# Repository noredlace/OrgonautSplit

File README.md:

# OrgonautSplit

A design by u/lizardsticks

A WIP split ergo board based off the orgonaut66. <br /> 

PCBs are mirrored to be utilized as a left and right.

KiCad Render

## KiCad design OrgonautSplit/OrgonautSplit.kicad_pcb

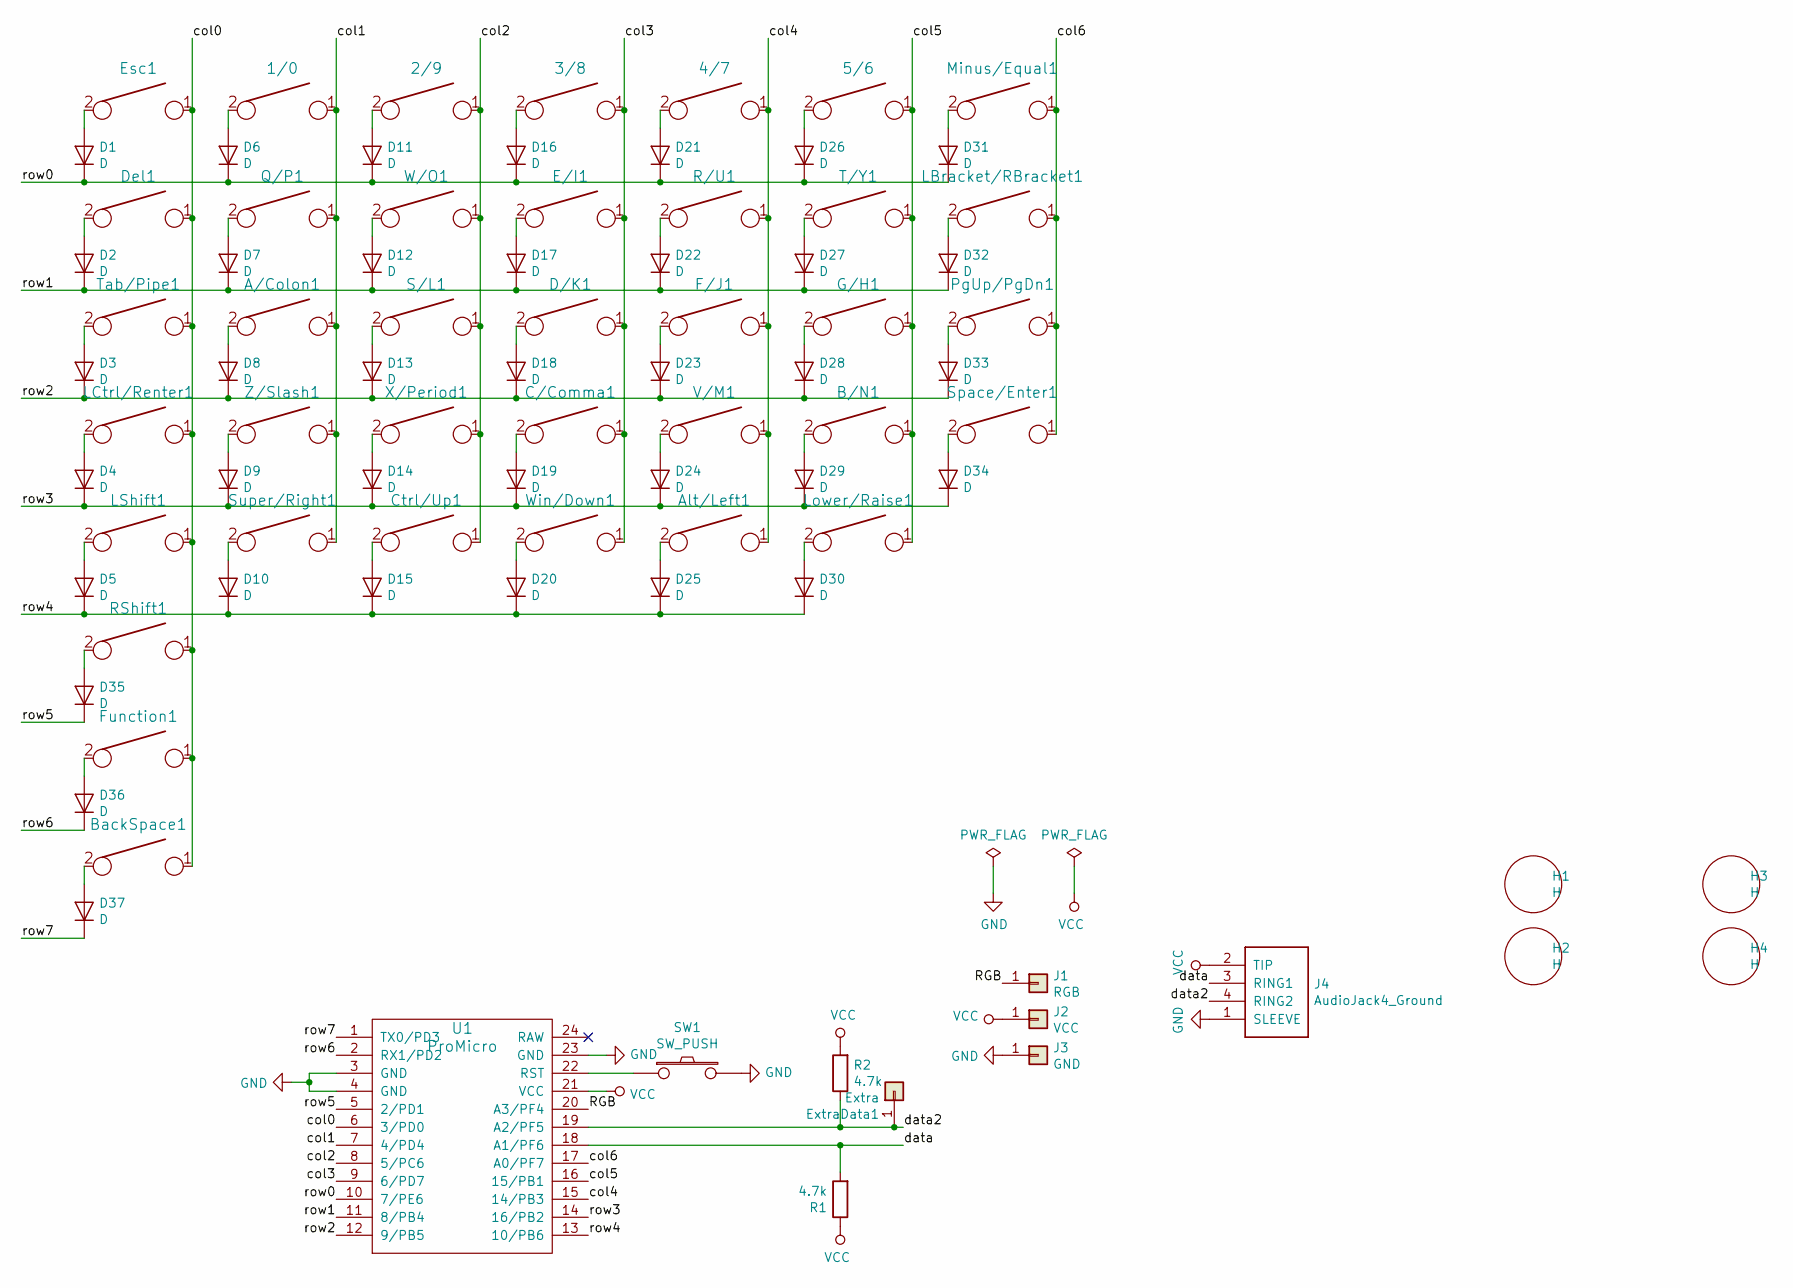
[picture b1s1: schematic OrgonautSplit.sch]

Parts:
1/0: One/Zero; Mx_Alps_100-dualside
2/9: Two/Nine; Mx_Alps_100-dualside
3/8: Three/Eight; Mx_Alps_100-dualside
4/7: Four/Seven; Mx_Alps_100-dualside
5/6: Five/Six; Mx_Alps_100-dualside
A/Colon1: A/Colon; Mx_Alps_100-dualside
Alt/Left1: Alt/Left; Mx_Alps_100-dualside
B/N1: B/N; Mx_Alps_100-dualside
BackSpace1: BackSpace; Mx_Alps_200
C/Comma1: C/Comma; Mx_Alps_100-dualside
Ctrl/Up1: Ctrl/Up; Mx_Alps_100-dualside
D1, D2, D3, D4, D5, D6, D7, D8, D9, D10, D11, D12, D13, D14, D15, D16, D17, D18, D19, D20, D21, D22, D23, D24, D25, D26, D27, D28, D29, D30, D31, D32, D33, D34, D35, D36, D37: D; Diode-Hybrid-Back
D/K1: D/K; Mx_Alps_100-dualside
Del1: Del; Mx_Alps_100
E/I1: E/I; Mx_Alps_100-dualside
Esc1: Esc; Mx_Alps_100
ExtraData1: Extra; SinglePad
F/J1: F/J; Mx_Alps_100-dualside
Function1: Function; Mx_Alps_100
G/H1: G/H; Mx_Alps_100-dualside
H1, H2, H3, H4: H; MountingHole
J1: RGB; SinglePad
J2: VCC; SinglePad
J3: GND; SinglePad
J4: AudioJack4_Ground; TRRS-PJ-320A-dual
LBracket/RBracket1: Brackets; Mx_Alps_100-dualside
LCtrl/Renter1: Ctrl/REnter; Hybrid_PCB_200H-dual
LShift1: LShift; Mx_Alps_275
Lower/Raise1: Lower/Raise; Mx_Alps_100-dualside
Minus/Equal1: Min/Eq; Mx_Alps_100-dualside
PgUp/PgDn1: PgUp/PgDn; Mx_Alps_100-dualside
Q/P1: Q/P; Mx_Alps_100-dualside
R1, R2: 4.7k; Resistor-Hybrid-Back
R/U1: R/U; Mx_Alps_100-dualside
RShift1: RShift; Mx_Alps_175
S/L1: S/L; Mx_Alps_100-dualside
SW1: SW_PUSH; SW_Tactile_SPST_Angled_MJTP1117
Space/Enter1: Space/Enter; Hybrid_PCB_200H-dual
Super/Right1: Super/Right; Mx_Alps_100-dualside
T/Y1: T/Y; Mx_Alps_100-dualside
Tab/Pipe1: Tab/Pipe; Mx_Alps_150-dualsided
U1: ProMicro; ArduinoProMicro-ZigZag
V/M1: V/M; Mx_Alps_100-dualside
W/O1: W/O; Mx_Alps_100-dualside
Win/Down1: Win/Down; Mx_Alps_100-dualside
X/Period1: X/Period; Mx_Alps_100-dualside
Z/Slash1: Z/Slash; Mx_Alps_100-dualside

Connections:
/RGB: J1.1, U1.20 (A3/PF4)
/col0: BackSpace1.1, Del1.1, Esc1.1, Function1.1, LCtrl/Renter1.1, LShift1.1, RShift1.1, Tab/Pipe1.1, U1.6 (3/PD0)
/col1: 1/0.1, A/Colon1.1, Q/P1.1, Super/Right1.1, U1.7 (4/PD4), Z/Slash1.1
/col2: 2/9.1, Ctrl/Up1.1, S/L1.1, U1.8 (5/PC6), W/O1.1, X/Period1.1
/col3: 3/8.1, C/Comma1.1, D/K1.1, E/I1.1, U1.9 (6/PD7), Win/Down1.1
/col4: 4/7.1, Alt/Left1.1, F/J1.1, R/U1.1, U1.15 (14/PB3), V/M1.1
/col5: 5/6.1, B/N1.1, G/H1.1, Lower/Raise1.1, T/Y1.1, U1.16 (15/PB1)
/col6: LBracket/RBracket1.1, Minus/Equal1.1, PgUp/PgDn1.1, Space/Enter1.1, U1.17 (A0/PF7)
/data: J4.3 (RING1), R1.2, U1.18 (A1/PF6)
/data2: ExtraData1.1, J4.4 (RING2), R2.1, U1.19 (A2/PF5)
/row0: D1.1 (K), D6.1 (K), D11.1 (K), D16.1 (K), D21.1 (K), D26.1 (K), D31.1 (K), U1.10 (7/PE6)
/row1: D2.1 (K), D7.1 (K), D12.1 (K), D17.1 (K), D22.1 (K), D27.1 (K), D32.1 (K), U1.11 (8/PB4)
/row2: D3.1 (K), D8.1 (K), D13.1 (K), D18.1 (K), D23.1 (K), D28.1 (K), D33.1 (K), U1.12 (9/PB5)
/row3: D4.1 (K), D9.1 (K), D14.1 (K), D19.1 (K), D24.1 (K), D29.1 (K), D34.1 (K), U1.14 (16/PB2)
/row4: D5.1 (K), D10.1 (K), D15.1 (K), D20.1 (K), D25.1 (K), D30.1 (K), U1.13 (10/PB6)
/row5: D35.1 (K), U1.5 (2/PD1)
/row6: D36.1 (K), U1.2 (RX1/PD2)
/row7: D37.1 (K), U1.1 (TX0/PD3)
GND: J3.1, J4.1 (SLEEVE), SW1.2, U1.3 (GND), U1.4 (GND), U1.23 (GND)
unnamed: 1/0.2, D6.2 (A)
unnamed: 2/9.2, D11.2 (A)
unnamed: 3/8.2, D16.2 (A)
unnamed: 4/7.2, D21.2 (A)
unnamed: 5/6.2, D26.2 (A)
unnamed: A/Colon1.2, D8.2 (A)
unnamed: Alt/Left1.2, D25.2 (A)
unnamed: B/N1.2, D29.2 (A)
unnamed: BackSpace1.2, D37.2 (A)
unnamed: C/Comma1.2, D19.2 (A)
unnamed: Ctrl/Up1.2, D15.2 (A)
unnamed: D1.2 (A), Esc1.2
unnamed: D2.2 (A), Del1.2
unnamed: D3.2 (A), Tab/Pipe1.2
unnamed: D4.2 (A), LCtrl/Renter1.2
unnamed: D5.2 (A), LShift1.2
unnamed: D7.2 (A), Q/P1.2
unnamed: D9.2 (A), Z/Slash1.2
unnamed: D10.2 (A), Super/Right1.2
unnamed: D12.2 (A), W/O1.2
unnamed: D13.2 (A), S/L1.2
unnamed: D14.2 (A), X/Period1.2
unnamed: D17.2 (A), E/I1.2
unnamed: D20.2 (A), Win/Down1.2
unnamed: D22.2 (A), R/U1.2
unnamed: D23.2 (A), F/J1.2
unnamed: D24.2 (A), V/M1.2
unnamed: D27.2 (A), T/Y1.2
unnamed: D28.2 (A), G/H1.2
unnamed: D30.2 (A), Lower/Raise1.2
unnamed: D31.2 (A), Minus/Equal1.2
unnamed: D32.2 (A), LBracket/RBracket1.2
unnamed: D33.2 (A), PgUp/PgDn1.2
unnamed: D34.2 (A), Space/Enter1.2
unnamed: D35.2 (A), RShift1.2
unnamed: D36.2 (A), Function1.2
unnamed: D18.2 (A), D/K1.2
unnamed: SW1.1, U1.22 (RST)
VCC: J2.1, J4.2 (TIP), R1.1, R2.2, U1.21 (VCC)

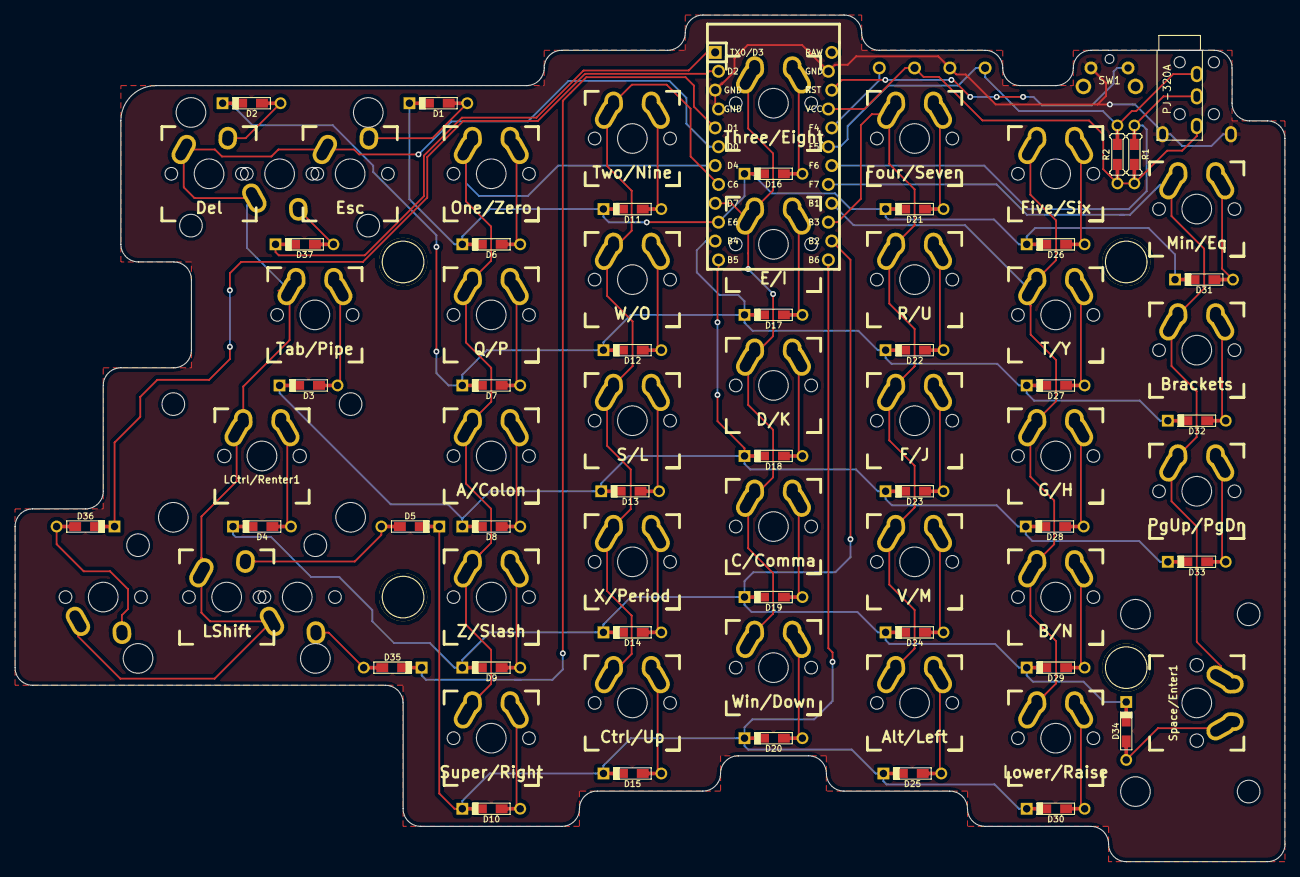
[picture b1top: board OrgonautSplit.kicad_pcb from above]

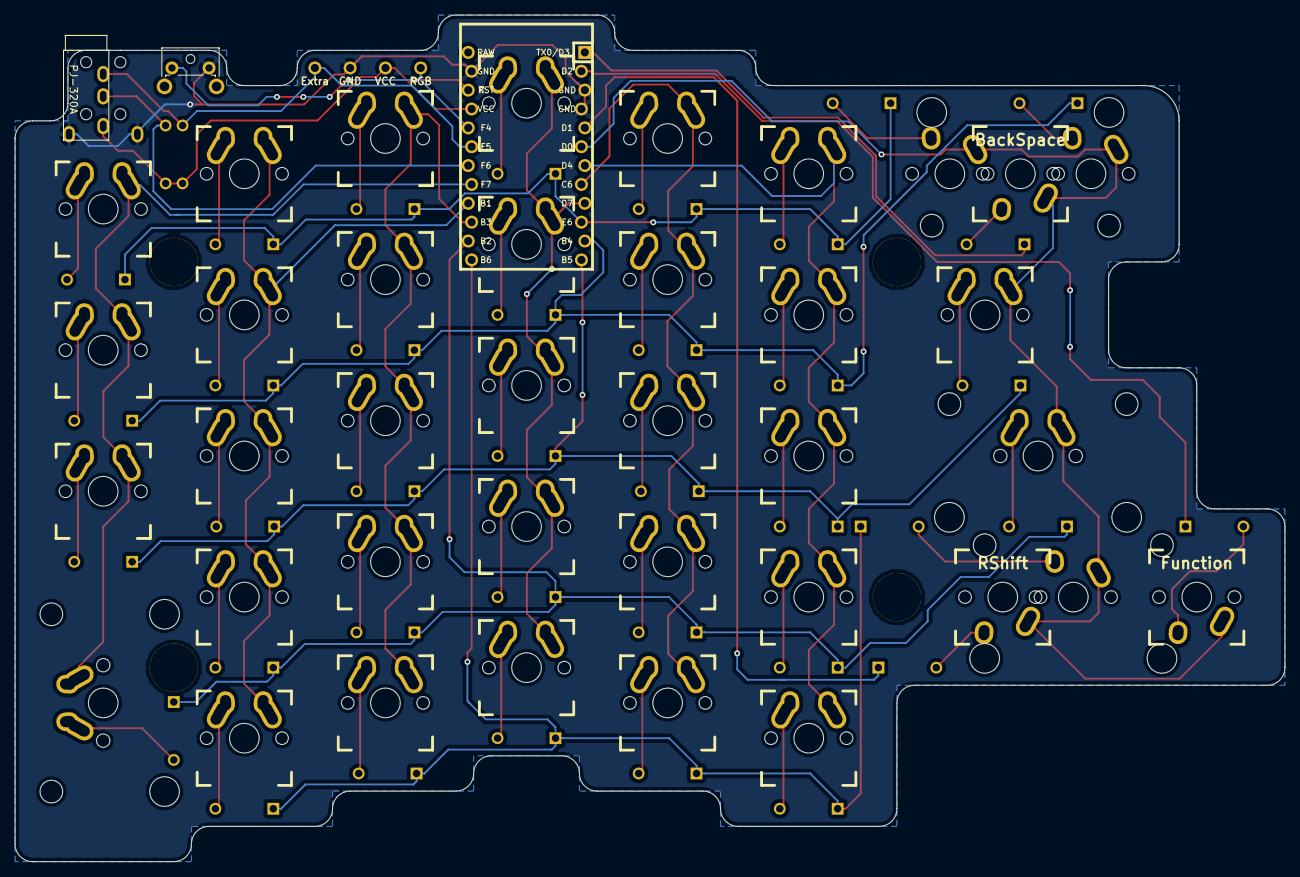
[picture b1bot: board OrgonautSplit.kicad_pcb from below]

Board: 2 copper layers, 171.0 x 114.0 mm, 87 parts (47 on the bottom side), 58 nets.

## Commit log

2019-03-02 add photo
